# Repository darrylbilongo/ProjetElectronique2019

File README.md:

# ProjetElectronique2019
Projet d'électronique 2TI

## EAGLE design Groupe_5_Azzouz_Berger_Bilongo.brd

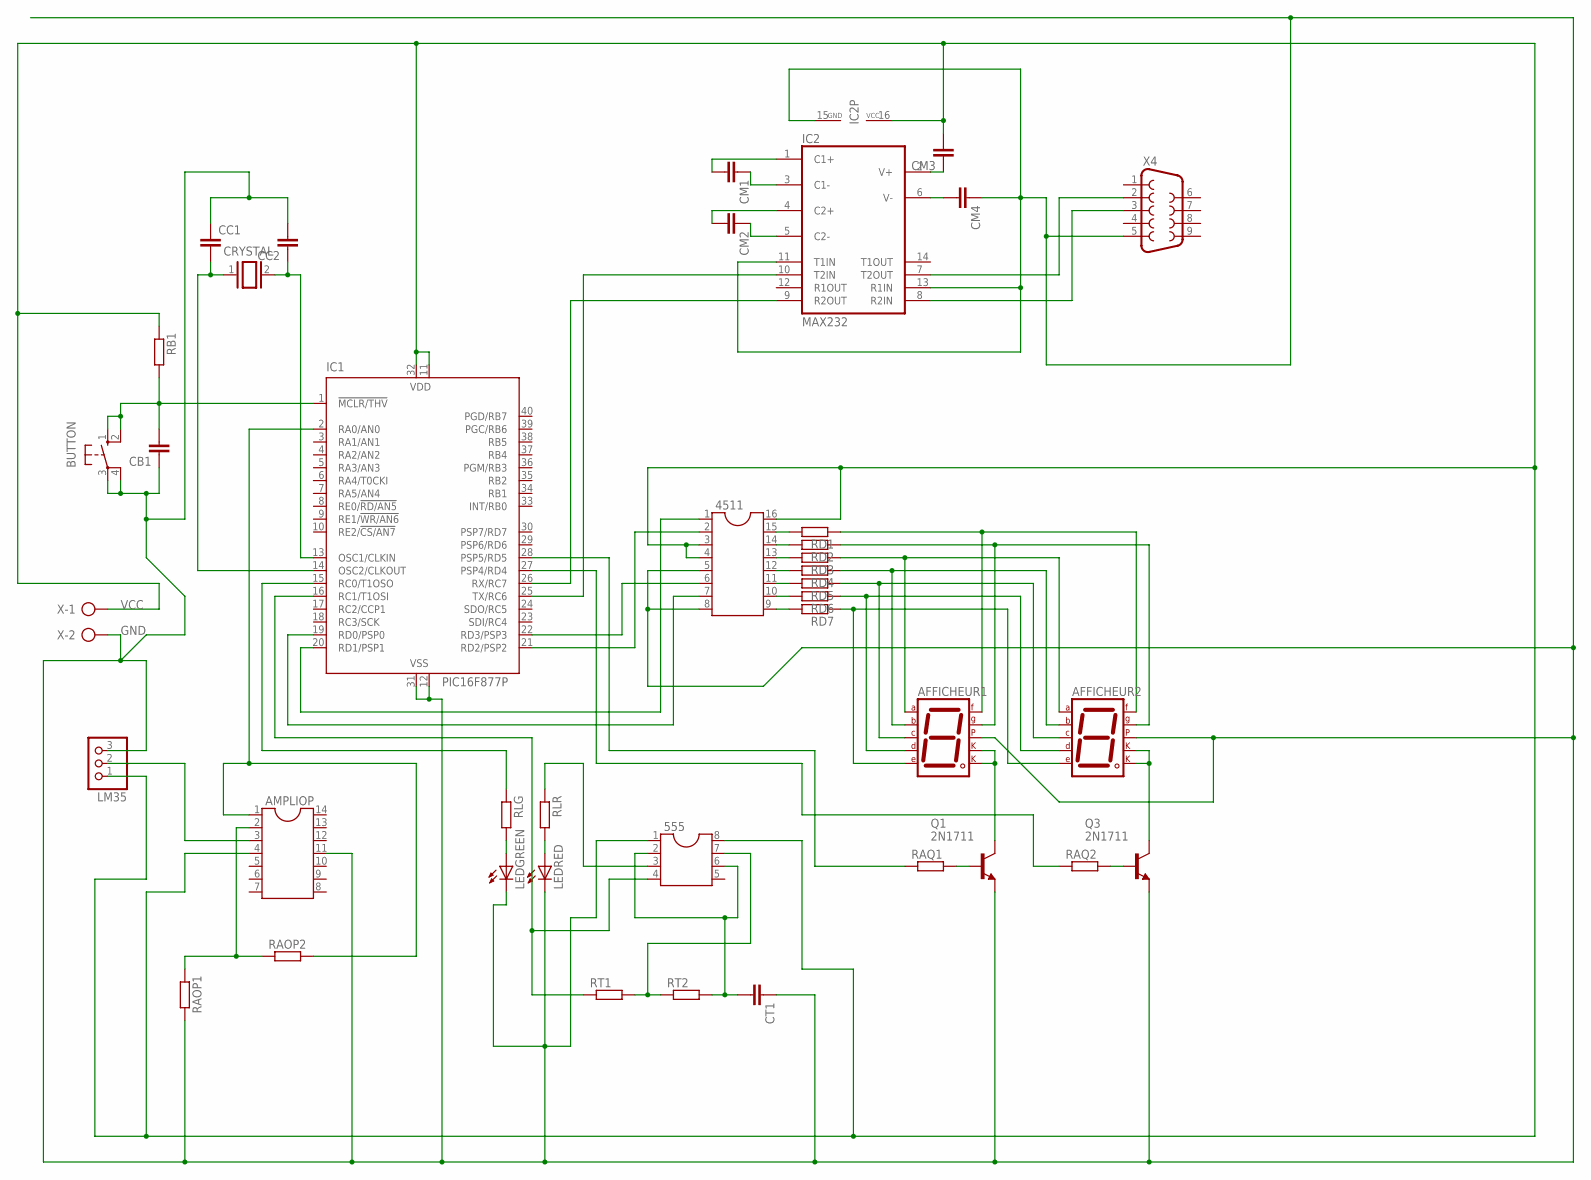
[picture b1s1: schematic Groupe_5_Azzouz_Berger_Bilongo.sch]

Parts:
555: DIL8; DIL08
4511: DIL16
AFFICHEUR1, AFFICHEUR2: 7SEG-CK; 7SEG-13
AMPLIOP: DIL14
BUTTON: 10-XX; B3F-10XX
CB1: C-EU025-050X050; C025-050X050
CC1, CC2: C-EU025-050X050; C025-050X050
CM1, CM2, CM3, CM4: C-EU025-050X050; C025-050X050
CRYSTAL: XTAL/S; QS
CT1: C-EU025-050X050; C025-050X050
IC1: PIC16F877P; DIL40
IC2: MAX232; DIL16
LEDGREEN: LED_ELD260; LED_LD260
LEDRED: LED_ELD260; LED_LD260
LM35: PINHD-1X3; 1X03
Q1, Q3: 2N1711; TO39
RAOP1, RAOP2: R-EU_0204/7; 0204/7
RAQ1, RAQ2: R-EU_0204/7; 0204/7
RB1: R-EU_0204/7; 0204/7
RD1, RD2, RD3, RD4, RD5, RD6, RD7: R-EU_0204/7; 0204/7
RLG: R-EU_0204/7; 0204/7
RLR: R-EU_0204/7; 0204/7
RT1, RT2: R-EU_0204/7; 0204/7
X: AK300/2
X4: F09V

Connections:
GND: 555.1, 4511.5, 4511.8, AFFICHEUR1.5 (DP), AFFICHEUR2.5 (DP), AMPLIOP.11, BUTTON.3, BUTTON.4 (P1), CB1.1, CC1.1, CC2.2, CM4.1, CT1.1, IC1.12 (VSS), IC1.31 (VSS), IC2.11 (T1IN), IC2.13 (R1IN), IC2.15 (GND), LEDGREEN.K (C), LEDRED.K (C), LM35.3, Q1.1 (E), Q3.1 (E), RAOP1.2, X.2, X4.5
unnamed: IC1.15 (RC0/T1OSO), RLG.1
unnamed: LEDGREEN.A, RLG.2
unnamed: BUTTON.1 (S), BUTTON.2 (S1), CB1.2, IC1.1 (!MCLR/THV), RB1.2
unnamed: 555.3, RLR.1
unnamed: CC1.2, CRYSTAL.1, IC1.14 (OSC2/CLKOUT)
unnamed: CC2.1, CRYSTAL.2, IC1.13 (OSC1/CLKIN)
unnamed: LEDRED.A, RLR.2
unnamed: AMPLIOP.3, LM35.2
unnamed: AMPLIOP.2, RAOP1.1, RAOP2.1
unnamed: AMPLIOP.1, IC1.2 (RA0/AN0), RAOP2.2
unnamed: 555.2, 555.6, CT1.2, RT2.2
unnamed: 555.7, RT1.2, RT2.1
unnamed: 555.4, IC1.16 (RC1/T1OSI), RT1.1
unnamed: 4511.6, IC1.22 (RD3/PSP3)
unnamed: 4511.2, IC1.21 (RD2/PSP2)
unnamed: 4511.15, RD1.2
unnamed: 4511.7, IC1.19 (RD0/PSP0)
unnamed: 4511.1, IC1.20 (RD1/PSP1)
unnamed: 4511.14, RD2.2
unnamed: 4511.13, RD3.2
unnamed: 4511.12, RD4.2
unnamed: 4511.11, RD5.2
unnamed: 4511.10, RD6.2
unnamed: 4511.9, RD7.2
unnamed: AFFICHEUR1.3 (CK1), AFFICHEUR1.8 (CK2), Q1.3 (C)
unnamed: AFFICHEUR2.3 (CK1), AFFICHEUR2.8 (CK2), Q3.3 (C)
unnamed: AFFICHEUR1.1 (E), AFFICHEUR2.1 (E), RD7.1
unnamed: AFFICHEUR1.2 (D), AFFICHEUR2.2 (D), RD6.1
unnamed: AFFICHEUR1.4 (C), AFFICHEUR2.4 (C), RD5.1
unnamed: AFFICHEUR1.6 (B), AFFICHEUR2.6 (B), RD4.1
unnamed: AFFICHEUR1.7 (A), AFFICHEUR2.7 (A), RD3.1
unnamed: AFFICHEUR1.10 (G), AFFICHEUR2.10 (G), RD2.1
unnamed: AFFICHEUR1.9 (F), AFFICHEUR2.9 (F), RD1.1
unnamed: Q1.2 (B), RAQ1.2
unnamed: Q3.2 (B), RAQ2.2
unnamed: IC1.28 (PSP5/RD5), RAQ1.1
unnamed: IC1.27 (PSP4/RD4), RAQ2.1
unnamed: CM3.1, IC2.2 (V+)
unnamed: CM1.2, IC2.1 (C1+)
unnamed: CM1.1, IC2.3 (C1-)
unnamed: CM2.2, IC2.4 (C2+)
unnamed: CM2.1, IC2.5 (C2-)
unnamed: CM4.2, IC2.6 (V-)
unnamed: IC1.25 (TX/RC6), IC2.10 (T2IN)
unnamed: IC1.26 (RX/RC7), IC2.9 (R2OUT)
unnamed: IC2.8 (R2IN), X4.3
unnamed: IC2.7 (T2OUT), X4.2
VCC: 555.8, 4511.3, 4511.4, 4511.16, AMPLIOP.4, CM3.2, IC1.11 (VDD), IC1.32 (VDD), IC2.16 (VCC), LM35.1, RB1.1, X.1

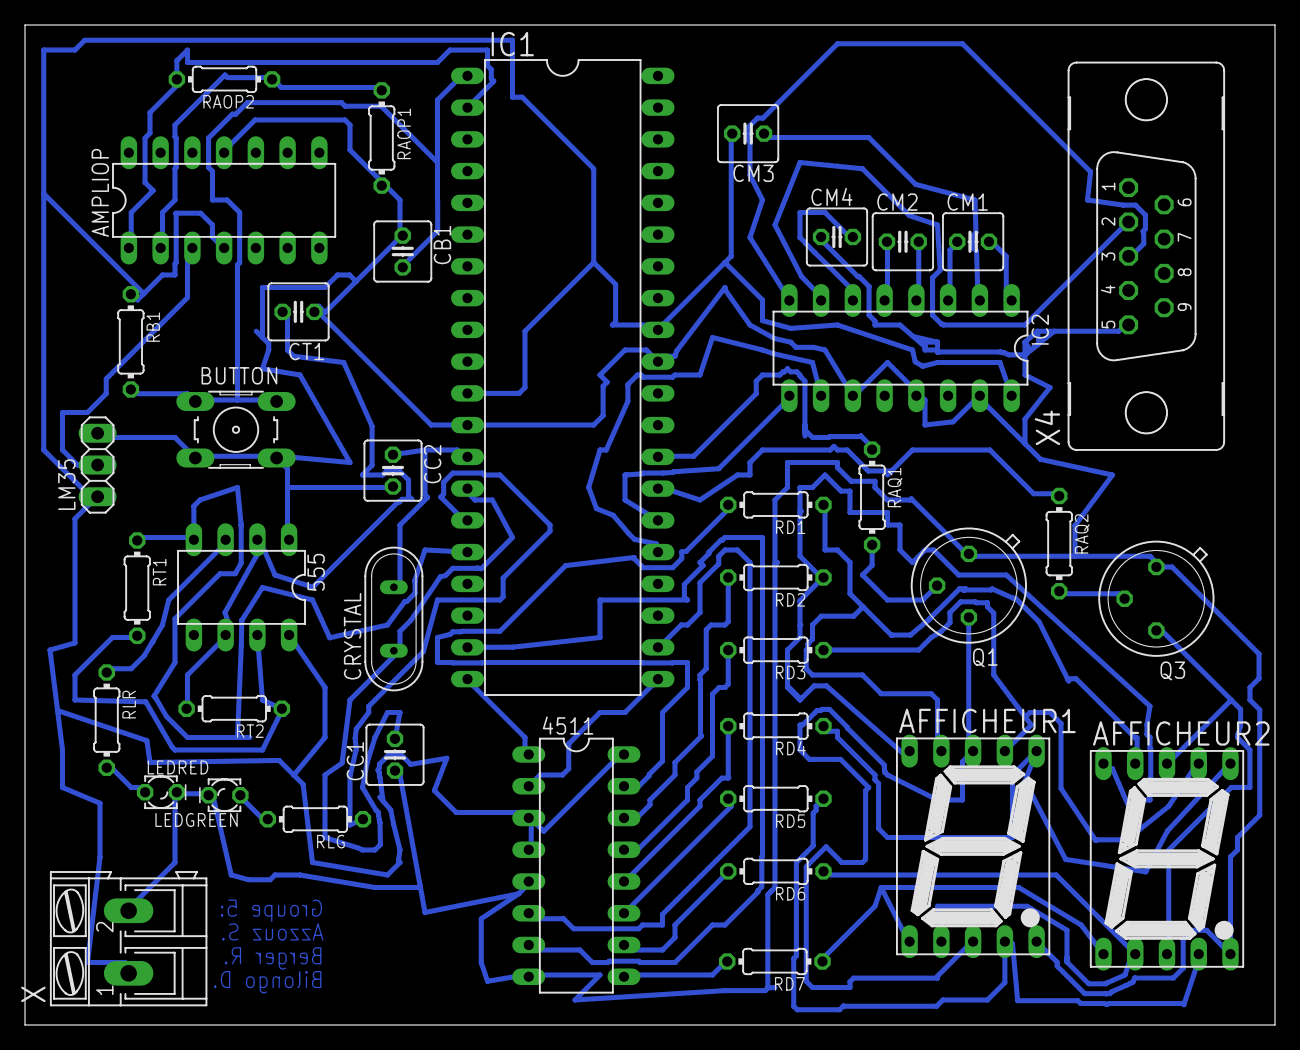
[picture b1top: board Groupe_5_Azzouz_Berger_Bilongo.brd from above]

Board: 2 copper layers, 100.0 x 80.0 mm, 40 parts (0 on the bottom side), 49 nets.

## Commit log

2019-05-19 Commit de l'application JAVA up to date(!)
